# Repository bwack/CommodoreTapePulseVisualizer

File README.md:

# CommodoreTapePulseVisualizer
Azimuth head alignment tool

Note, Rev 1.0 of the PCB is not tested yet.

## YouTube

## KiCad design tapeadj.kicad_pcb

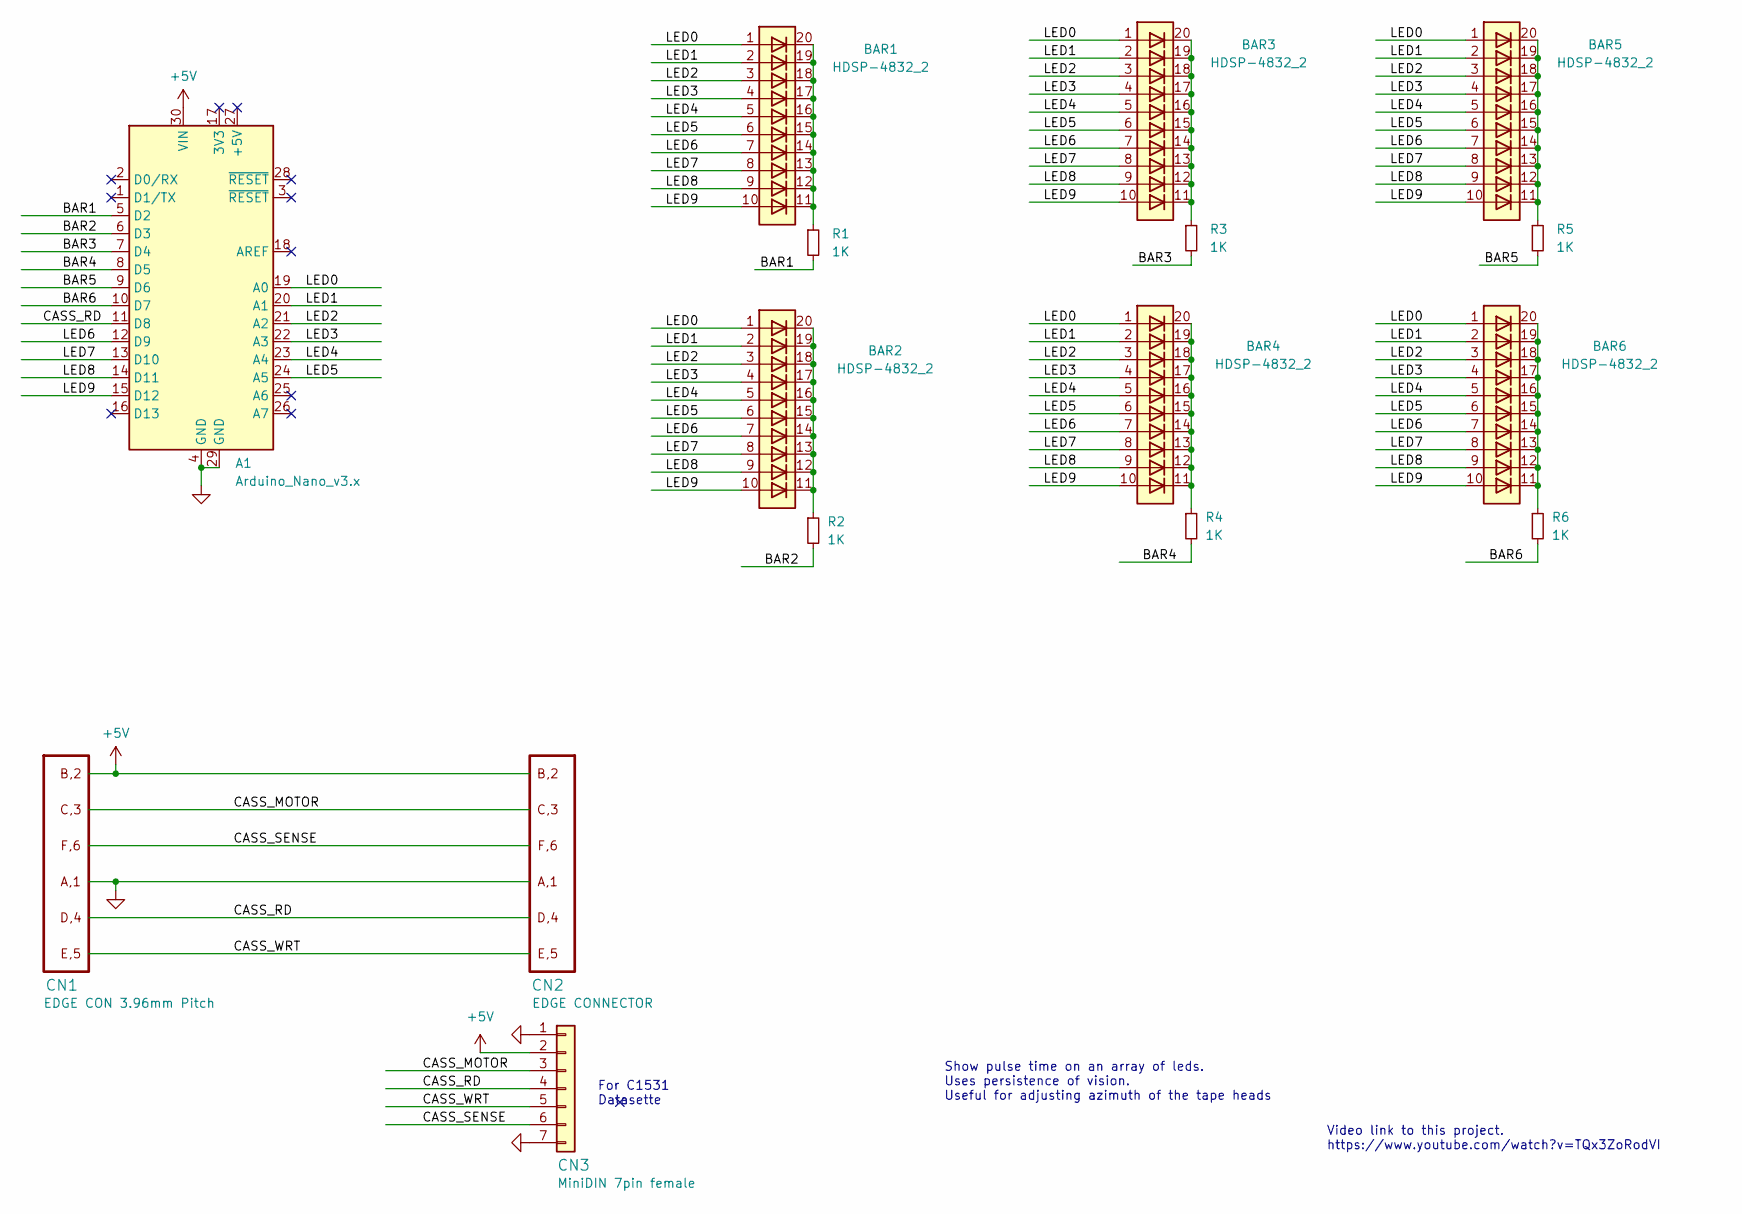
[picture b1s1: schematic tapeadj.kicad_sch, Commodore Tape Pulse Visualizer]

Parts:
A1: Arduino_Nano_v3.x; Arduino_Nano
BAR1, BAR2, BAR3, BAR4, BAR5, BAR6: HDSP-4832_2; HDSP-4832
CN1: EDGE CON 3.96mm Pitch; EDGE_CON_FEMALE_12P_TAPE
CN2: EDGE CONNECTOR; EDGE_CON_12P_TAPE
CN3: MiniDIN 7pin female; CUI_MD-70S
R1, R2, R3, R4, R5, R6: 1K; R_Axial_DIN0207_L6.3mm_D2.5mm_P10.16mm_Horizontal

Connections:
+5V: A1.30 (VIN), CN1.2, CN1.B, CN2.2, CN2.B, CN3.2
/BAR1: A1.5 (D2), R1.2
/BAR2: A1.6 (D3), R2.2
/BAR3: A1.7 (D4), R3.2
/BAR4: A1.8 (D5), R4.2
/BAR5: A1.9 (D6), R5.2
/BAR6: A1.10 (D7), R6.2
/CASS_MOTOR: CN1.3, CN1.C, CN2.3, CN2.C, CN3.3
/CASS_RD: A1.11 (D8), CN1.4, CN1.D, CN2.4, CN2.D, CN3.4
/CASS_SENSE: CN1.6, CN1.F, CN2.6, CN2.F, CN3.6
/CASS_WRT: CN1.5, CN1.E, CN2.5, CN2.E, CN3.5
/LED0: A1.19 (A0), BAR1.1 (A), BAR2.1 (A), BAR3.1 (A), BAR4.1 (A), BAR5.1 (A), BAR6.1 (A)
/LED1: A1.20 (A1), BAR1.2 (A), BAR2.2 (A), BAR3.2 (A), BAR4.2 (A), BAR5.2 (A), BAR6.2 (A)
/LED2: A1.21 (A2), BAR1.3 (A), BAR2.3 (A), BAR3.3 (A), BAR4.3 (A), BAR5.3 (A), BAR6.3 (A)
/LED3: A1.22 (A3), BAR1.4 (A), BAR2.4 (A), BAR3.4 (A), BAR4.4 (A), BAR5.4 (A), BAR6.4 (A)
/LED4: A1.23 (A4), BAR1.5 (A), BAR2.5 (A), BAR3.5 (A), BAR4.5 (A), BAR5.5 (A), BAR6.5 (A)
/LED5: A1.24 (A5), BAR1.6 (A), BAR2.6 (A), BAR3.6 (A), BAR4.6 (A), BAR5.6 (A), BAR6.6 (A)
/LED6: A1.12 (D9), BAR1.7 (A), BAR2.7 (A), BAR3.7 (A), BAR4.7 (A), BAR5.7 (A), BAR6.7 (A)
/LED7: A1.13 (D10), BAR1.8 (A), BAR2.8 (A), BAR3.8 (A), BAR4.8 (A), BAR5.8 (A), BAR6.8 (A)
/LED8: A1.14 (D11), BAR1.9 (A), BAR2.9 (A), BAR3.9 (A), BAR4.9 (A), BAR5.9 (A), BAR6.9 (A)
/LED9: A1.15 (D12), BAR1.10 (A), BAR2.10 (A), BAR3.10 (A), BAR4.10 (A), BAR5.10 (A), BAR6.10 (A)
GND: A1.4 (GND), A1.29 (GND), CN1.1, CN1.A, CN2.1, CN2.A, CN3.1, CN3.7
unnamed: BAR1.11 (K), BAR1.12 (K), BAR1.13 (K), BAR1.14 (K), BAR1.15 (K), BAR1.16 (K), BAR1.17 (K), BAR1.18 (K), BAR1.19 (K), BAR1.20 (K), R1.1
unnamed: BAR2.11 (K), BAR2.12 (K), BAR2.13 (K), BAR2.14 (K), BAR2.15 (K), BAR2.16 (K), BAR2.17 (K), BAR2.18 (K), BAR2.19 (K), BAR2.20 (K), R2.1
unnamed: BAR3.11 (K), BAR3.12 (K), BAR3.13 (K), BAR3.14 (K), BAR3.15 (K), BAR3.16 (K), BAR3.17 (K), BAR3.18 (K), BAR3.19 (K), BAR3.20 (K), R3.1
unnamed: BAR4.11 (K), BAR4.12 (K), BAR4.13 (K), BAR4.14 (K), BAR4.15 (K), BAR4.16 (K), BAR4.17 (K), BAR4.18 (K), BAR4.19 (K), BAR4.20 (K), R4.1
unnamed: BAR5.11 (K), BAR5.12 (K), BAR5.13 (K), BAR5.14 (K), BAR5.15 (K), BAR5.16 (K), BAR5.17 (K), BAR5.18 (K), BAR5.19 (K), BAR5.20 (K), R5.1
unnamed: BAR6.11 (K), BAR6.12 (K), BAR6.13 (K), BAR6.14 (K), BAR6.15 (K), BAR6.16 (K), BAR6.17 (K), BAR6.18 (K), BAR6.19 (K), BAR6.20 (K), R6.1

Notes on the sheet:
Video link to this project. https://www.youtube.com/watch?v=TQx3ZoRodVI
Show pulse time on an array of leds. Uses persistence of vision. Useful for adjusting azimuth of the tape heads
For C1531 Datasette

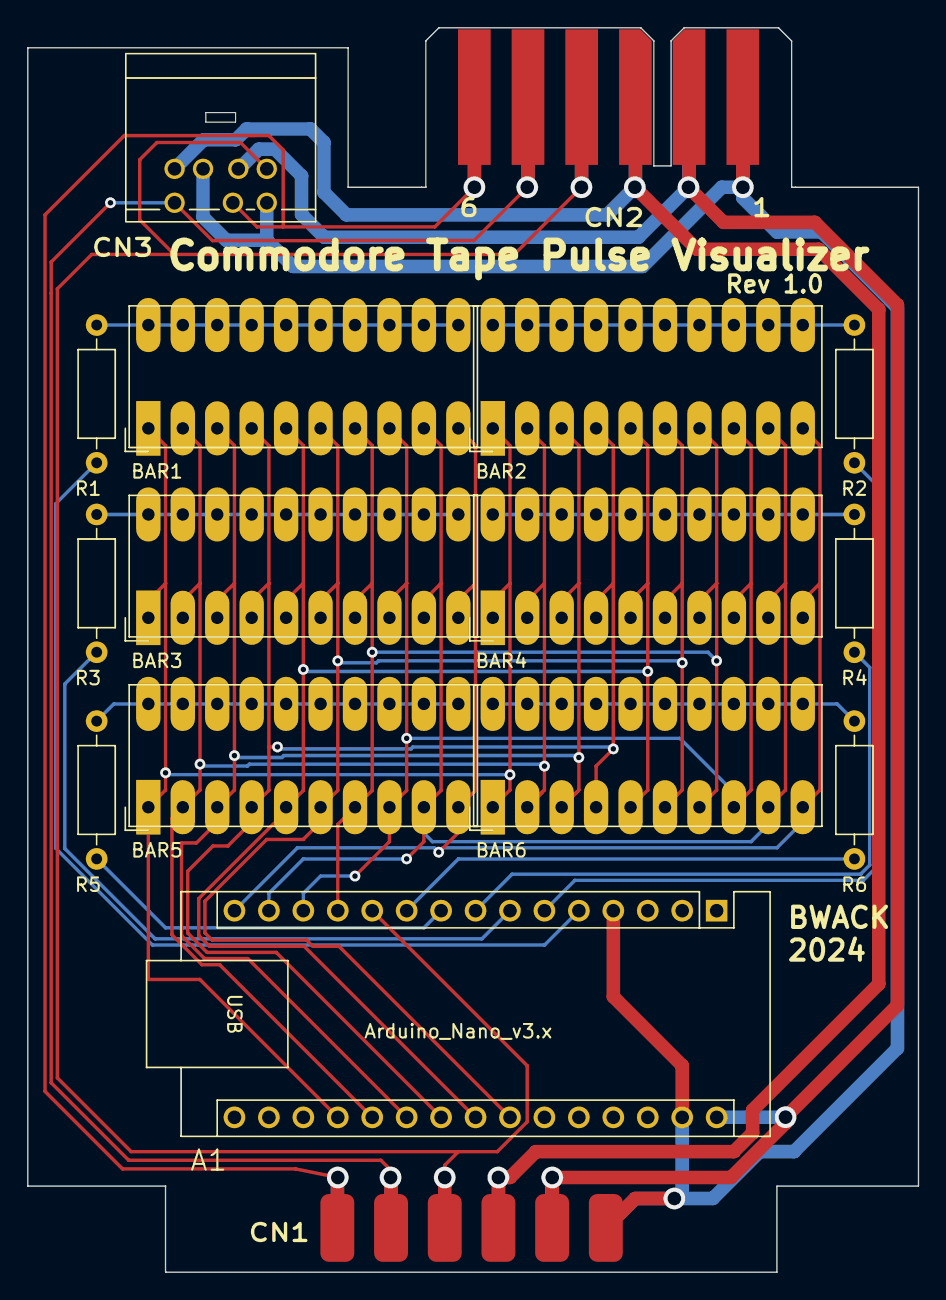
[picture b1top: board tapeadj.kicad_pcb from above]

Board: 2 copper layers, 65.7 x 91.8 mm, 16 parts (0 on the bottom side), 28 nets.

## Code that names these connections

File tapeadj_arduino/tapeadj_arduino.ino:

// Measures the HIGH width, LOW width, frequency, and duty-cycle of a pulse train
// on Arduino UNO Pin 8 (ICP1 pin).  

// Note: Since this uses Timer1, Pin 9 and Pin 10 can't be used for
// analogWrite().

/*
 * BAR1: D2, PD2
 * BAR2: D3, PD3
 * BAR3: D4, PD4
 * BAR4: D5, PD5
 * BAR5: D6, PD6
 * BAR6: D7, PD7
 * 
 * LED0: A0, PC0
 * LED1: A1, PC1
 * LED2: A2, PC2
 * LED3: A3, PC3
 * LED4: A4, PC4
 * LED5: A5, PC5
 * LED6: D9, PB1
 * LED7: D10, PB2
 * LED8: D11, PB3
 * LED9: D12, PB4
 * 
 * CASSRD: D8 (ICP1/PB0). Special interrupt capture pin
 * 
 * Note: A6 and A7 are inputs only.
 */


#define BAR1 PD2
#define BAR2 PD3
#define BAR3 PD4
#define BAR4 PD5
#define BAR5 PD6
#define BAR6 PD7
#define LED0 PC0

char a = 1;
char plex = 1;

void display(uint8_t v)
{
  uint8_t val=v%10;
  // Serial.println(v);
  // Serial.println(val);
  if (val<6) {
    PORTC=1<<val;
    PORTB=0;
  } else {
    PORTB= 1<<(val-5);
    PORTC=0;
  }

  PORTD=0;
  if (v<10) {
    DDRD = 1<<BAR1;
  }
  else if (v<20) {
    DDRD = 1<<BAR2;
  }
  else if (v<30) {
    DDRD = 1<<BAR3;
  }
  else if (v<40) {
    DDRD = 1<<BAR4;
  }
  else if (v<50) {
    DDRD = 1<<BAR5;
  }
  else {
    DDRD = 1<<BAR6;    
  }

}

void setup()
{
  Serial.begin(115200);
  while (!Serial);

  char count=0;
  DDRC = 0b00111111;
  DDRD = 0b11001100;
  DDRB = 0b00011110;
  for (uint8_t count=0; count<60; count++) {
    display(count);
    delay(40);
  }
  //delay(100);

  // For testing, uncomment one of these lines and connect
  // Pin 3 or Pin 5 to Pin 8
  // analogWrite(3, 64);  // 512.00, 1528.00, 2040.00, 25.10%, 490.20 Hz
  // analogWrite(5, 64);  // 260.00, 764.00, 1024.00, 25.39%, 976.56 Hz

  noInterrupts ();  // protected code
  // reset Timer 1
  TCCR1A = 0;
  TCCR1B = 0;
  TCNT1 = 0;
  TIMSK1 = 0;

  TIFR1 |= _BV(ICF1); // clear Input Capture Flag so we don't get a bogus interrupt
  TIFR1 |= _BV(TOV1); // clear Overflow Flag so we don't get a bogus interrupt

  TCCR1B = _BV(CS10) | // start Timer 1, no prescaler
           _BV(ICES1); // Input Capture Edge Select (1=Rising, 0=Falling)

  TIMSK1 |= _BV(ICIE1); // Enable Timer 1 Input Capture Interrupt
  TIMSK1 |= _BV(TOIE1); // Enable Timer 1 Overflow Interrupt
  interrupts ();
}

volatile uint32_t PulseHighTime = 0;
volatile uint32_t PulseLowTime = 0;
volatile uint16_t Overflows = 0;

ISR(TIMER1_OVF_vect)
{
  Overflows++;
}

ISR(TIMER1_CAPT_vect)
{
  static uint32_t firstRisingEdgeTime = 0;
  static uint32_t fallingEdgeTime = 0;
  static uint32_t secondRisingEdgeTime = 0;

  uint16_t overflows = Overflows;

  // If an overflow happened but has not been handled yet
  // and the timer count was close to zero, count the
  // overflow as part of this time.
  //if ((TIFR1 & _BV(TOV1)) && (ICR1 < 1024))
  if ((TIFR1 & _BV(TOV1)))
    overflows++;

  if (PulseLowTime == 0)
  {
    if (TCCR1B & _BV(ICES1))
    {
      // Interrupted on Rising Edge
      if (firstRisingEdgeTime)
      {
        // ... so this is the second rising edge, ending the low part
        // of the cycle.
        secondRisingEdgeTime = overflows; // Upper 16 bits
        secondRisingEdgeTime = (secondRisingEdgeTime << 16) | ICR1;
        PulseLowTime = secondRisingEdgeTime - fallingEdgeTime;
        firstRisingEdgeTime = 0;
      }
      else
      {
        firstRisingEdgeTime = overflows; // Upper 16 bits
        firstRisingEdgeTime = (firstRisingEdgeTime << 16) | ICR1;
        TCCR1B &= ~_BV(ICES1); // Switch to Falling Edge
      }
    }
    else
    {
      // Interrupted on Falling Edge
      fallingEdgeTime = overflows; // Upper 16 bits
      fallingEdgeTime = (fallingEdgeTime << 16) | ICR1;
      TCCR1B |= _BV(ICES1); // Switch to Rising Edge
      PulseHighTime = fallingEdgeTime - firstRisingEdgeTime;
    }
  }
}

void loop()
{

  noInterrupts();
  uint32_t pulseHighTime = PulseHighTime;
  uint32_t pulseLowTime = PulseLowTime;
  interrupts();

  // If a sample has been measured
  if (pulseLowTime)
  {
/*
    if ((pulseHighTime>>4 < 200) && (pulseHighTime>>4 > 120 )) {
    // Display the pulse length in microseconds
    Serial.print("High time (microseconds): ");
    Serial.println(pulseHighTime / 16.0, 2);
    Serial.print("Low time (microseconds): ");
    Serial.println(pulseLowTime / 16.0, 2);

    uint32_t cycleTime = pulseHighTime + pulseLowTime;
    Serial.print("Cycle time (microseconds): ");
    Serial.println(cycleTime / 16.0, 2);
    Serial.println(cycleTime>>4);

    float dutyCycle = pulseHighTime / (float)cycleTime;
    Serial.print("Duty cycle (%): ");
    Serial.println(dutyCycle * 100.0, 2);

    float frequency = (float)F_CPU / cycleTime;
    Serial.print("Frequency (Hz): ");
    Serial.println(frequency, 2);
    Serial.println();

    //uint32_t diff = 8 + 1000 - cycleTime/16;
    int32_t pulselen_measured = pulseHighTime>>4;
    uint8_t factual_pulselen = pulselen_measured > 155 ? 183 : 130;
    int32_t diff = ( pulselen_measured*100 - factual_pulselen*100)/factual_pulselen;
    diff = 8 - diff/2;
    Serial.println(diff);
    Serial.println(pulselen_measured);

*/    
    display(PulseHighTime>>7);
    //delay(1);

    // Request another sample
    noInterrupts();
    PulseLowTime = 0;
    interrupts();
  }

}

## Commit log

2024-02-04 rev 1.0
2024-02-04 Add the arduino program
2024-02-04 disable serial printing in display()
2024-02-04 Turn off delays. display faster!
